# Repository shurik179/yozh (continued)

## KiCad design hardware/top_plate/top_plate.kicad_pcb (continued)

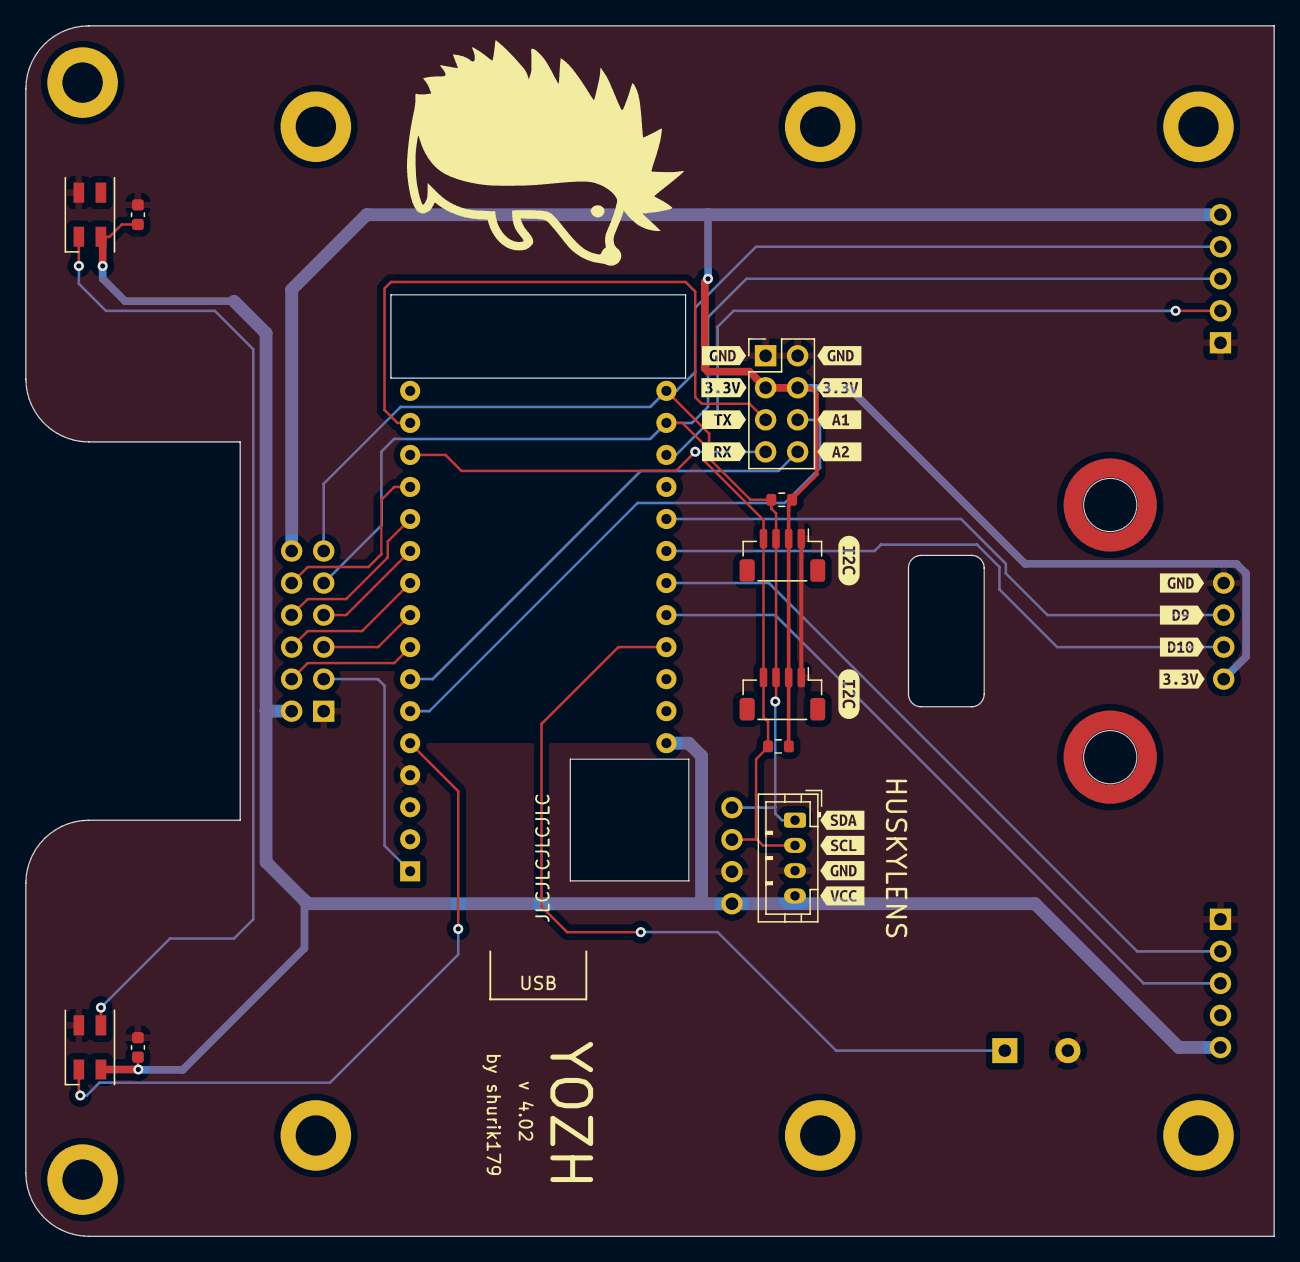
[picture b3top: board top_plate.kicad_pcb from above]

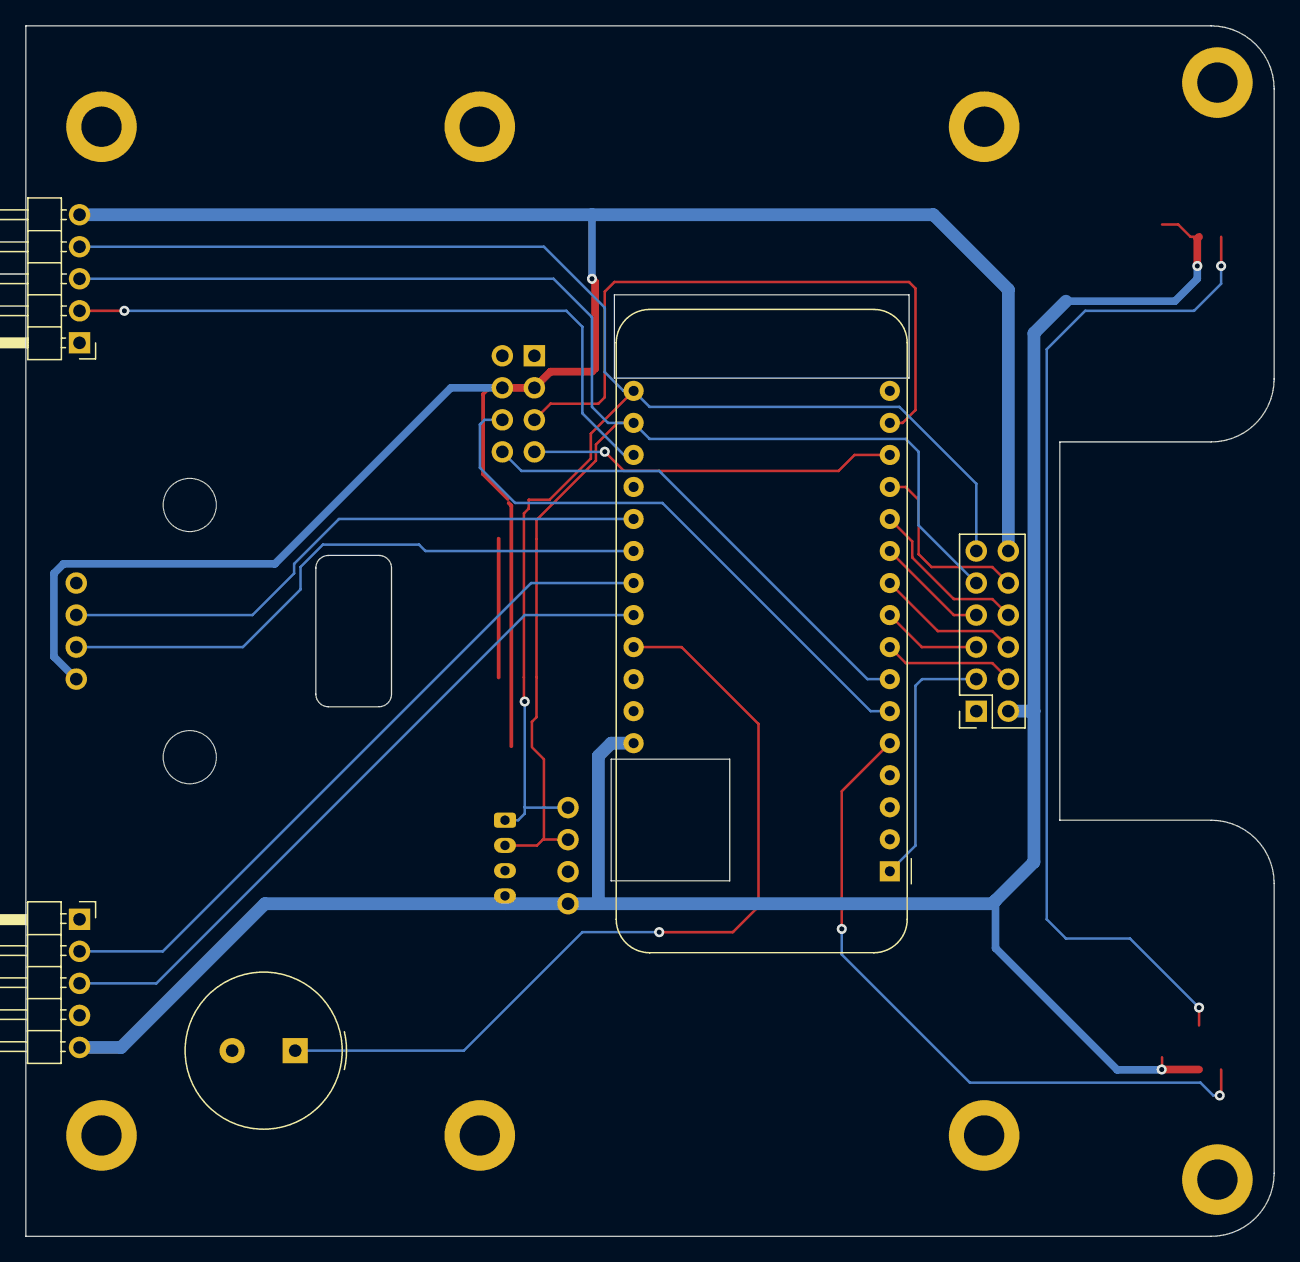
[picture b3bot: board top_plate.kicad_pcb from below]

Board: 2 copper layers, 99.0 x 96.0 mm, 37 parts (5 on the bottom side), 24 nets.

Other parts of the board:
M1, M2: SMTSO3035; mounting_SMD_NUT_M3_H6mm
kibuzzard-653BCB65, kibuzzard-653BCB65#2: G***; kibuzzard-653BCB65
kibuzzard-653BCCF1, kibuzzard-653BCCF1#2: G***; kibuzzard-653BCCF1
kibuzzard-653BCD2B: G***; kibuzzard-653BCD2B
kibuzzard-653BCD4B: G***; kibuzzard-653BCD4B
kibuzzard-653BCD42: G***; kibuzzard-653BCD42
kibuzzard-653BCDC1, kibuzzard-653BCDC1#2: G***; kibuzzard-653BCDC1
kibuzzard-653BCDD4: G***; kibuzzard-653BCDD4
kibuzzard-653BCDDF: G***; kibuzzard-653BCDDF
kibuzzard-653BCDE7: G***; kibuzzard-653BCDE7
kibuzzard-653BCECF: G***; kibuzzard-653BCECF
kibuzzard-653BCED5: G***; kibuzzard-653BCED5
kibuzzard-653BCEE0: G***; kibuzzard-653BCEE0
kibuzzard-653BCF3B: G***; kibuzzard-653BCF3B
kibuzzard-653BCF4B: G***; kibuzzard-653BCF4B
kibuzzard-653BCF42: G***; kibuzzard-653BCF42

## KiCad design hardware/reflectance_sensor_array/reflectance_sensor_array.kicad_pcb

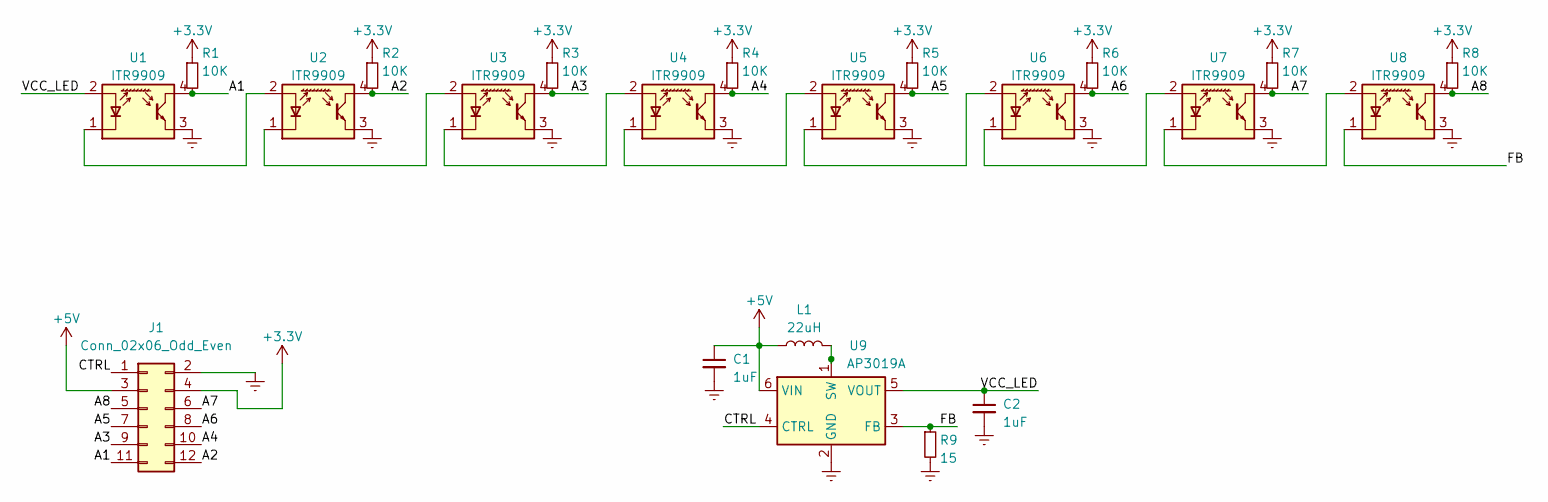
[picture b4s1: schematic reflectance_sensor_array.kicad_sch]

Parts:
C1, C2: 1uF; C_0603_1608Metric
J1: Conn_02x06_Odd_Even; PinHeader_2x06_P2.54mm_Vertical
L1: 22uH; L_Taiyo-Yuden_NR-60xx
R1, R2, R3, R4, R5, R6, R7, R8: 10K; R_0603_1608Metric
R9: 15; R_0603_1608Metric
U1, U2, U3, U4, U5, U6, U7, U8: ITR9909; Everlight_ITR9909
U9: AP3019A; TSOT-23-6

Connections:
+3V3: J1.4, R1.1, R2.1, R3.1, R4.1, R5.1, R6.1, R7.1, R8.1
+5V: C1.1, J1.3, L1.1, U9.6 (VIN)
/A1: J1.11, R1.2, U1.4 (C)
/A2: J1.12, R2.2, U2.4 (C)
/A3: J1.9, R3.2, U3.4 (C)
/A4: J1.10, R4.2, U4.4 (C)
/A5: J1.7, R5.2, U5.4 (C)
/A6: J1.8, R6.2, U6.4 (C)
/A7: J1.6, R7.2, U7.4 (C)
/A8: J1.5, R8.2, U8.4 (C)
/CTRL: J1.1, U9.4 (CTRL)
/FB: R9.1, U8.1 (K), U9.3 (FB)
/VCC_LED: C2.1, U1.2 (A), U9.5 (VOUT)
GNDREF: C1.2, C2.2, J1.2, R9.2, U1.3 (E), U2.3 (E), U3.3 (E), U4.3 (E), U5.3 (E), U6.3 (E), U7.3 (E), U8.3 (E), U9.2 (GND)
unnamed: L1.2, U9.1 (SW)
unnamed: U1.1 (K), U2.2 (A)
unnamed: U2.1 (K), U3.2 (A)
unnamed: U3.1 (K), U4.2 (A)
unnamed: U4.1 (K), U5.2 (A)
unnamed: U5.1 (K), U6.2 (A)
unnamed: U6.1 (K), U7.2 (A)
unnamed: U7.1 (K), U8.2 (A)

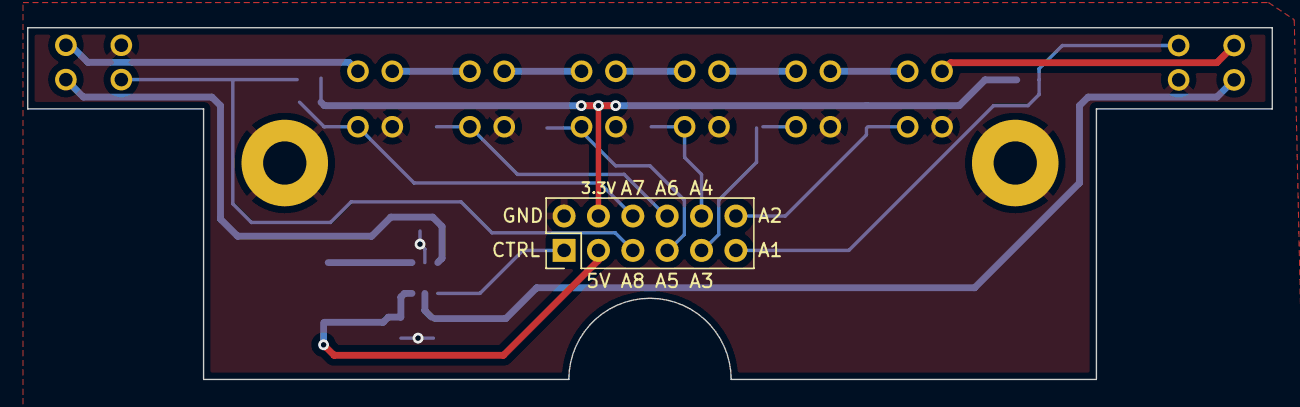
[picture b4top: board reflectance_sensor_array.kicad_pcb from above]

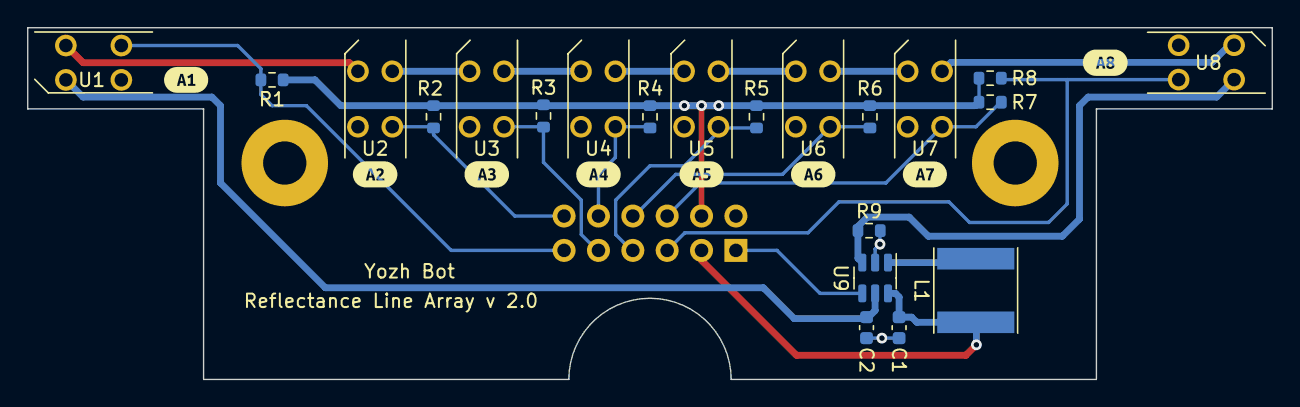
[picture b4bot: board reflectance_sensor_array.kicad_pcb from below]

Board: 2 copper layers, 92.0 x 26.0 mm, 30 parts (29 on the bottom side), 22 nets.

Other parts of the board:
svg2mod, svg2mod#2, svg2mod#3, svg2mod#4, svg2mod#5, svg2mod#6, svg2mod#7, svg2mod#8: G***; svg2mod

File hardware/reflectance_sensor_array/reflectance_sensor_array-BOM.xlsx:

Component | Description | Part Number | References | Value | Footprint | Quantity Per PCB | Side | Datasheet | LCSC | Comment
1 | SMD capacitor, 0603, 1uF |  | C1 C2 | 1uF | C_0603_1608Metric | 2 | Bottom | ~ | C15849 | generic
2 | 2*6 male header, 0.1", 15mm length |  | J1 | Conn_02x06_Odd_Even | PinHeader_2x06_P2.54mm_Vertical | 1 | Top | https://www.aliexpress.com/item/32893947629.html?spm=a2g0s.9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 |  | 2*40 header broken into 2*6 pieces
3 | Inductor, 22uH | NRS6014T220MMGG | L1 | 22uH | L_Taiyo-Yuden_NR-60xx | 1 | Bottom | ~ | C222982
4 | SMD resistor, 0603, 15 Ohm |  | R9 | 15 | R_0603_1608Metric | 1 | Bottom | ~ | C22810 | generic
5 | SMD resistor, 0603, 10K |  | R1 R2 R3 R4 R5 R6 R7 R8 | 10K | R_0603_1608Metric | 8 | Bottom | ~ | C25804 | generic
6 | White LED Step-Up Converter, 1.2Mhz, TSOT23-6 | AP3019AKTR | U9 | AP3019A | TSOT-23-6 | 1 | Bottom | https://www.diodes.com/assets/Datasheets/AP3019A.pdf | C44956
7 | Subminiature Reflective Optical Sensor, DIP-like THT-package | ITR9909 | U1 U2 U3 U4 U5 U6 U7 U8 | ITR9909 | Everlight_ITR9909 | 8 | Bottom | https://everlighteurope.com/index.php?controller=attachment&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 | C53399

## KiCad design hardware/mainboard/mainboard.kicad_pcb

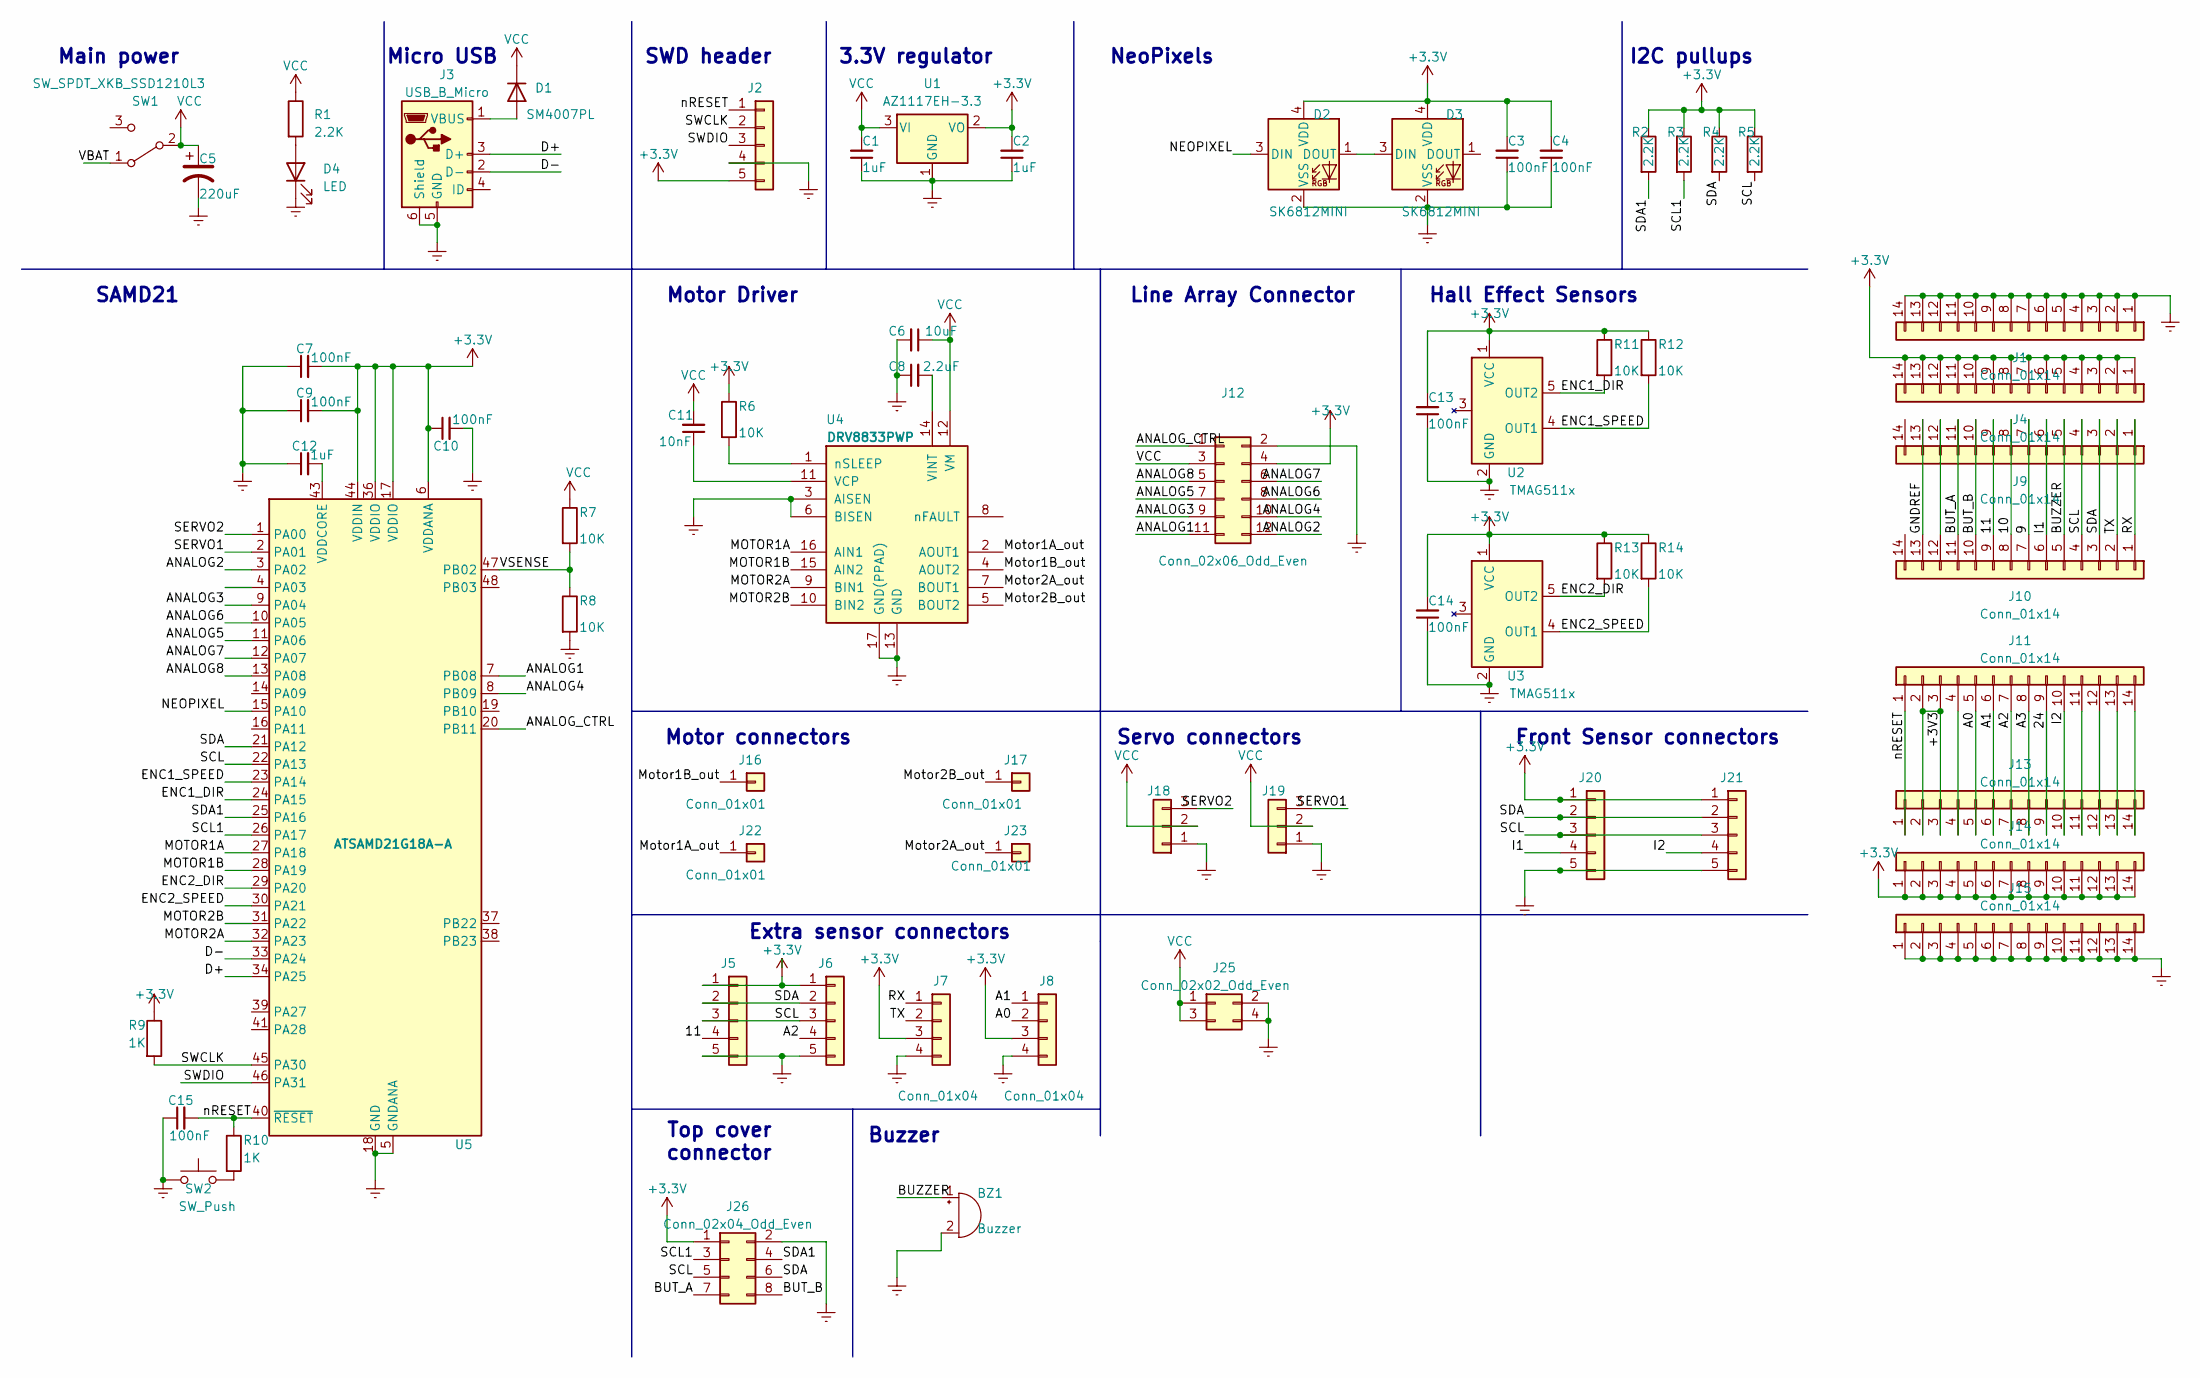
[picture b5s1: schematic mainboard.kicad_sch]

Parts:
BZ1: Buzzer; Buzzer_TDK_PS1240P02BT_D12.2mm_H6.5mm
C1, C2, C12: 1uF; C_0603_1608Metric; LCSC C15849
C3, C4, C7, C9, C10, C13, C14, C15: 100nF; C_0603_1608Metric; LCSC C14663
C5: 220uF; C_Radial_D8.0mm_H7.0mm_P3.50mm
C6: 10uF; C_0805_2012Metric; LCSC C15850
C8: 2.2uF; C_0603_1608Metric; LCSC C23630
C11: 10nF; C_0603_1608Metric; LCSC C57112
D1: SM4007PL; D_SOD-123F; LCSC C64898
D2, D3: SK6812MINI; LED_SK6812MINI_PLCC4_3.5x3.5mm_P1.75mm
D4: LED; LED_0603_1608Metric
J1, J4, J9, J13, J14, J15: Conn_01x14; PinHeader_1x14_P2.54mm_Vertical
J2: Conn_01x05; PinSocket_1x05_P2.54mm_Lock
J3: USB_B_Micro; USB_Micro-B_Amphenol_10118194_Horizontal; LCSC C145779
J5, J6, J20, J21: Conn_01x05; PinHeader_1x05_P2.54mm_Vertical
J7, J8: Conn_01x04; JST_PH_B4B-PH-K_1x04_P2.00mm_Vertical
J10, J11: Conn_01x14; PinSocket_1x14_P2.54mm_Vertical
J12: Conn_02x06_Odd_Even; PinSocket_2x06_P2.54mm_Vertical
J16, J17, J22, J23: Conn_01x01; connector-1p-generic-nosilk
J18, J19: Conn_01x03; PinHeader_1x03_P2.54mm_Vertical
J25: Conn_02x02_Odd_Even; PinHeader_2x02_P2.54mm_Vertical
J26: Conn_02x04_Odd_Even; PinSocket_2x04_P2.54mm_Vertical
R1: 2.2K; R_0603_1608Metric; LCSC C21190
R2, R3, R4, R5: 2.2K; R_0603_1608Metric; LCSC C4190
R6, R7, R8, R11, R12, R13, R14: 10K; R_0603_1608Metric; LCSC C25804
R9, R10: 1K; R_0603_1608Metric; LCSC C21190
SW1: SW_SPDT_XKB_SSD1210L3; SW_XKB_SS12D10L3
SW2: SW_Push; SW_SPST_HRO-K2-1808SN
U1: AZ1117EH-3.3; SOT-223; LCSC C108494
U2, U3: TMAG511x; SOT-23-5
U4: DRV8833PWP; HTSSOP-16-1EP_4.4x5mm_P0.65mm_EP3.4x5mm_Mask2.46x2.31mm_The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; LCSC C50506
U5: ATSAMD21G18A-A; QFP-48_7x7_Pitch0.5mm_reduced

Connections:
/9: J9.7, J10.7
/10: J9.8, J10.8
/11: J5.4, J9.9, J10.9
/24: J11.9, J13.9
/A0: J8.2, J11.5, J13.5
/A1: J8.1, J11.6, J13.6
/A2: J6.4, J11.7, J13.7
/A3: J11.8, J13.8
/ANALOG1: J12.11, U5.7 (PB08)
/ANALOG2: J12.12, U5.3 (PA02)
/ANALOG3: J12.9, U5.9 (PA04)
/ANALOG4: J12.10, U5.8 (PB09)
/ANALOG5: J12.7, U5.11 (PA06)
/ANALOG6: J12.8, U5.10 (PA05)
/ANALOG7: J12.6, U5.12 (PA07)
/ANALOG8: J12.5, U5.13 (PA08)
/ANALOG_CTRL: J12.1, U5.20 (PB11)
/BUT_A: J9.11, J10.11, J26.7
/BUT_B: J9.10, J10.10, J26.8
/BUZZER: BZ1.1 (-), J9.5, J10.5
/D+: J3.3 (D+), U5.34 (PA25)
/D-: J3.2 (D-), U5.33 (PA24)
/ENC1_DIR: R11.2, U2.5 (OUT2), U5.24 (PA15)
/ENC1_SPEED: R12.2, U2.4 (OUT1), U5.23 (PA14)
/ENC2_DIR: R13.2, U3.5 (OUT2), U5.29 (PA20)
/ENC2_SPEED: R14.2, U3.4 (OUT1), U5.30 (PA21)
/I1: J9.6, J10.6, J20.4
/I2: J11.10, J13.10, J21.4
/MOTOR1A: U4.16 (AIN1), U5.27 (PA18)
/MOTOR1B: U4.15 (AIN2), U5.28 (PA19)
/MOTOR2A: U4.9 (BIN1), U5.32 (PA23)
/MOTOR2B: U4.10 (BIN2), U5.31 (PA22)
/Motor1A_out: J22.1, U4.2 (AOUT1)
/Motor1B_out: J16.1, U4.4 (AOUT2)
/Motor2A_out: J23.1, U4.7 (BOUT1)
/Motor2B_out: J17.1, U4.5 (BOUT2)
/NEOPIXEL: D2.3 (DIN), U5.15 (PA10)
/RX: J7.1, J9.1, J10.1
/SCL: J5.3, J6.3, J9.4, J10.4, J20.3, J21.3, J26.5, R5.2, U5.22 (PA13)
/SCL1: J26.3, R3.2, U5.26 (PA17)
/SDA: J5.2, J6.2, J9.3, J10.3, J20.2, J21.2, J26.6, R4.2, U5.21 (PA12)
/SDA1: J26.4, R2.2, U5.25 (PA16)
/SERVO1: J19.3, U5.2 (PA01)
/SERVO2: J18.3, U5.1 (PA00)
/SWCLK: J2.2, R9.2, U5.45 (PA30)
/SWDIO: J2.3, U5.46 (PA31)
/TX: J7.2, J9.2, J10.2
/VBAT: SW1.1 (A)
/VSENSE: R7.2, R8.1, U5.47 (PB02)
/nRESET: C15.2, J2.1, J11.1, J13.1, R10.1, U5.40 (~RESET)
GNDREF: BZ1.2 (+), C1.1, C2.1, C3.1, C4.1, C5.2, C6.2, C7.1, C8.1, C9.1, C10.2, C12.1, C13.1, C14.1, C15.1, D2.2 (VSS), D3.2 (VSS), D4.1 (K), J1.1, J1.2, J1.3, J1.4, J1.5, J1.6, J1.7, J1.8, J1.9, J1.10, J1.11, J1.12, J1.13, J1.14, J2.4, J3.5 (GND), J3.6 (Shield), J5.5, J6.5, J7.4, J8.4, J9.13, J10.13, J12.2, J15.1, J15.2, J15.3, J15.4, J15.5, J15.6, J15.7, J15.8, J15.9, J15.10, J15.11, J15.12, J15.13, J15.14, J18.1, J19.1, J20.5, J21.5, J25.2, J25.4, J26.2, R8.2, SW2.1, U1.1 (GND), U2.2 (GND), U3.2 (GND), U4.3 (AISEN), U4.6 (BISEN), U4.13 (GND), U4.17 (GND(PPAD)), U5.5 (GNDANA), U5.18 (GND), U5.35 (GND), U5.42 (GND)
unnamed: C8.2, U4.14 (VINT)
unnamed: C11.1, U4.11 (VCP)
unnamed: C12.2, U5.43 (VDDCORE)
unnamed: D1.2 (A), J3.1 (VBUS)
unnamed: D2.1 (DOUT), D3.3 (DIN)
unnamed: D4.2 (A), R1.2
unnamed: J9.12, J10.12
unnamed: J11.4, J13.4
unnamed: J11.11, J13.11
unnamed: J11.12, J13.12
unnamed: J11.13, J13.13
unnamed: J11.14, J13.14
unnamed: R6.2, U4.1 (nSLEEP)
unnamed: R10.2, SW2.2
VCC: C1.2, C5.1, C6.1, C11.2, D1.1 (K), J12.3, J18.2, J19.2, J25.1, J25.3, R1.1, R7.1, SW1.2 (B), U1.3 (VI), U4.12 (VM)

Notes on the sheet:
Hall Effect Sensors
Extra sensor connectors
Line Array Connector
SWD header
3.3V regulator
Top cover connector
Servo connectors
Front Sensor connectors
NeoPixels
Motor Driver
SAMD21
Main power
Motor connectors
I2C pullups
Buzzer
Micro USB

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
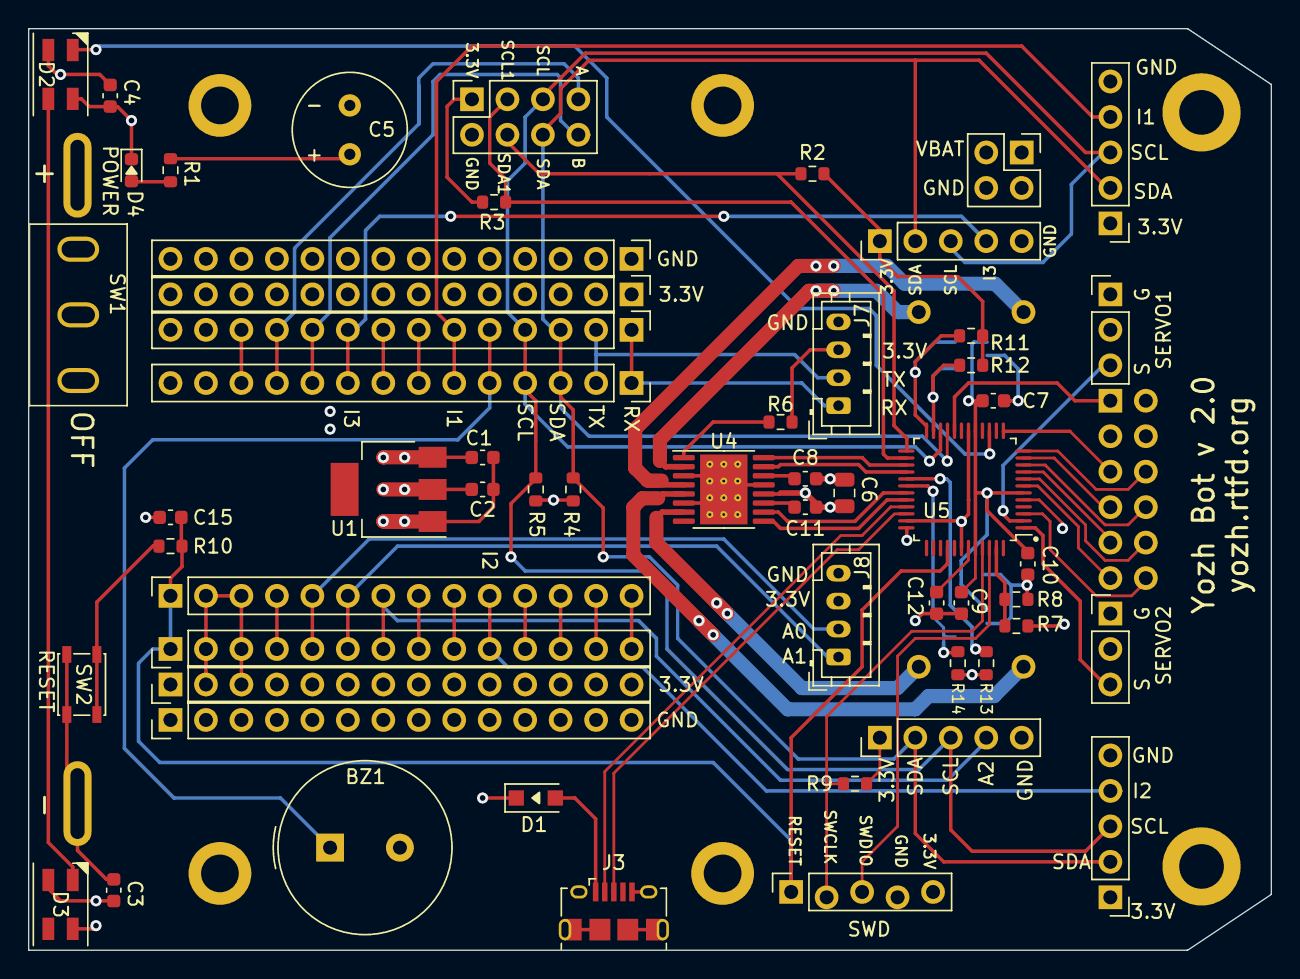
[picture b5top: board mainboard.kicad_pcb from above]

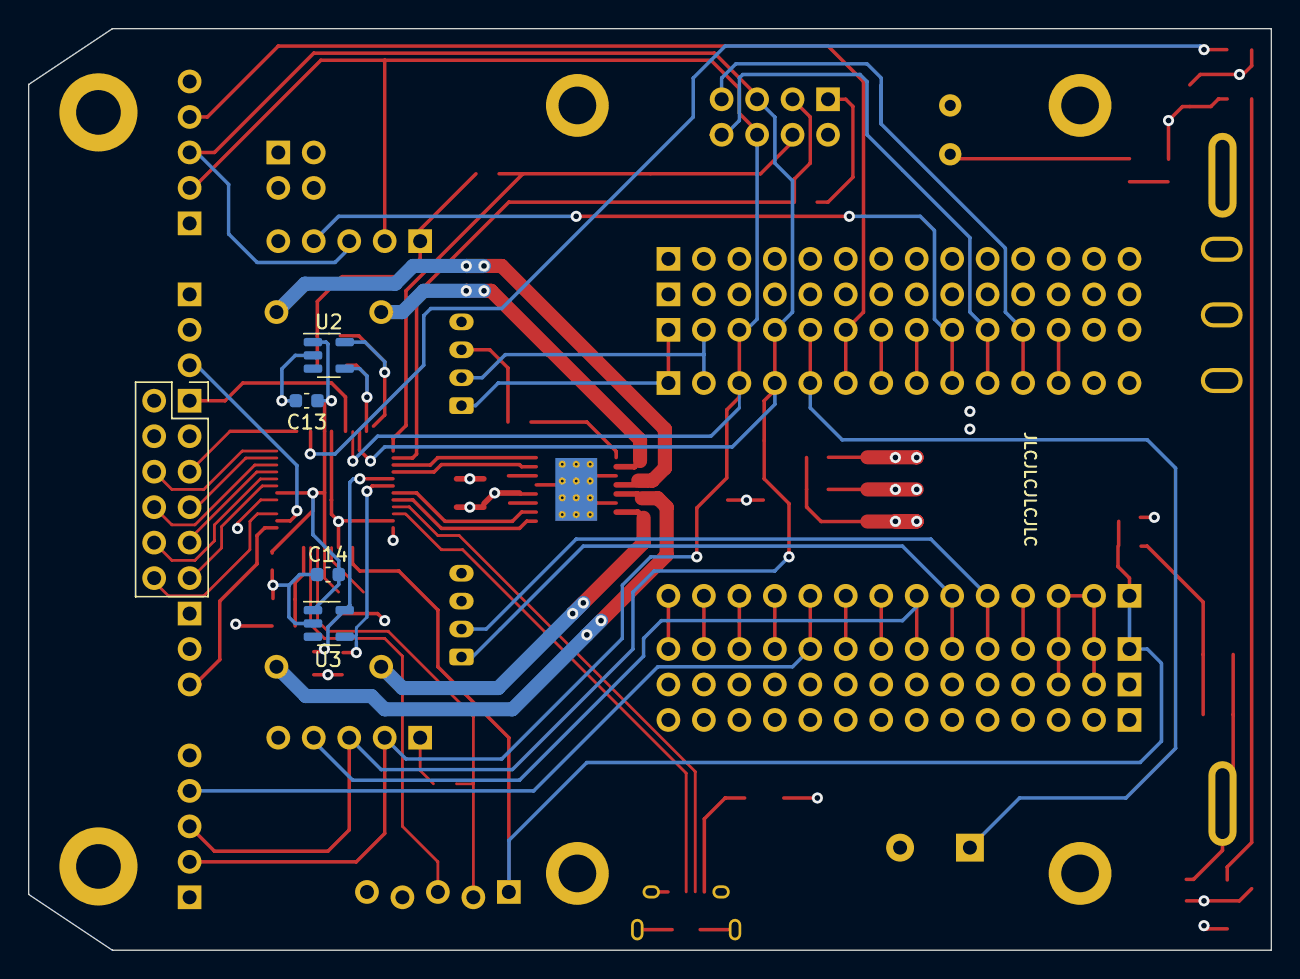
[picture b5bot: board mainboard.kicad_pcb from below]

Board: 4 copper layers, 89.0 x 66.0 mm, 66 parts (5 on the bottom side), 66 nets.

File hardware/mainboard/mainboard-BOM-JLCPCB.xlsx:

Comment | Designator | Footprint | LCSC
10nF | C11 | 0603 | C57112
100nF | C3 C4 C7 C9 C10 C15 | 0603 | C14663
1uF | C1 C2 C12 | 0603 | C15849
2.2uF | C8 | 0603 | C23630
10uF | C6 | 0805 | C15850
220uF | C5 | C_Radial_D8.0mm_H7.0mm_P3.50mm | C45072
LED, Green | D4 | LED_0603_1608Metric | C72043
SM4007PL | D1 | D_SOD-123F | C64898
 | J3 | USB_Micro-B_Amphenol_10118194_Horizontal | C132563
1K | R9 R10 | 0603 | C21190
2.2K | R1 R2 R3 R4 R5 | 0603 | C4190
10K | R6 R7 R8 R11 R12 R13 R14 | 0603 | C25804
 | SW2 | SW_SPST_HRO-K2-1808SN | C92589
 | SW1 | SW_XKB_SS12D10L3 | C319013
ATSAMD21G18A-AU | U5 | QFP-48_7x7_Pitch0.5mm_reduced | C78624
AZ1117EH-3.3TRG1 | U1 | SOT-223 | C108494
DRV8833PWP | U4 | HTSSOP-16-1EP_4.4x5mm_P0.65mm_EP3.4x5mm_Mask2.46x2.31mm_ThermalVias_reduced | C50506
 | BZ1 | Buzzer_TDK_PS1240P02BT_D12.2mm_H6.5mm | C76871

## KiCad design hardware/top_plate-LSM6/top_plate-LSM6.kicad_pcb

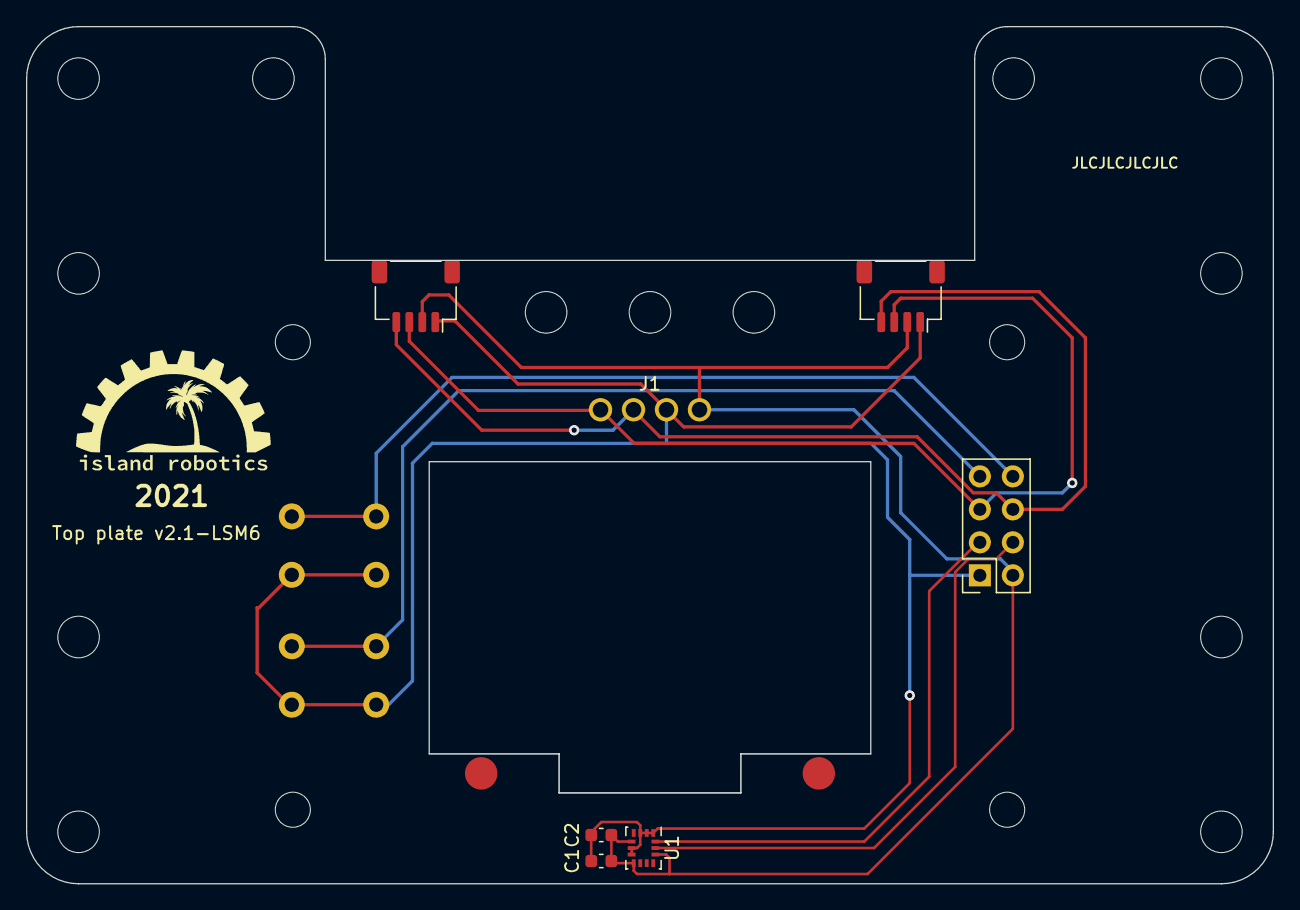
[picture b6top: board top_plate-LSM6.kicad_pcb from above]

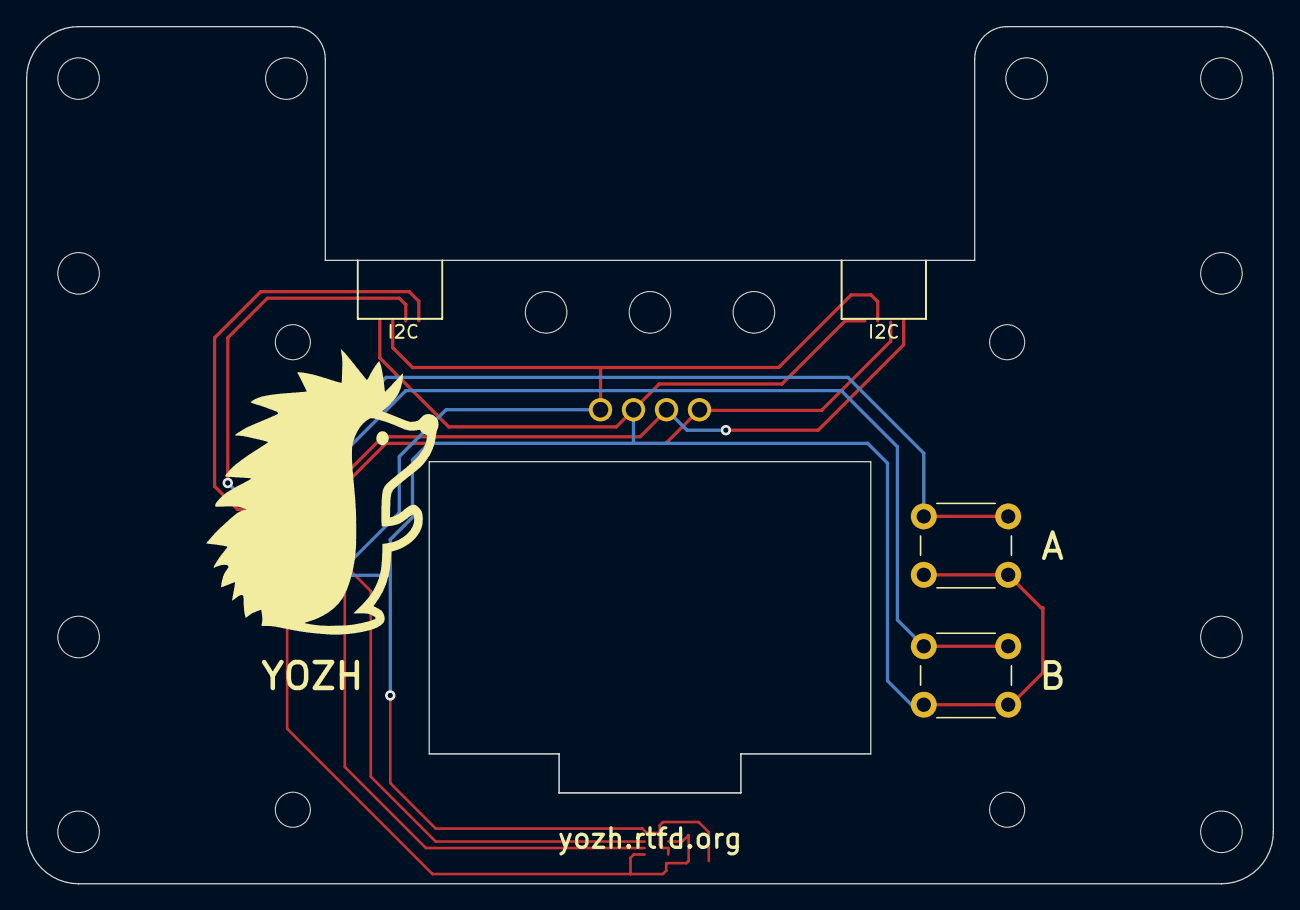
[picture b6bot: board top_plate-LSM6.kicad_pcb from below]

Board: 2 copper layers, 96.0 x 66.0 mm, 9 parts (2 on the bottom side), 8 nets.

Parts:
C1, C2: 100nF; C_0603_1608Metric
J1: Conn_01x04_Male; OLED_128x64_1_3in
J2, J3: Conn_01x04; JST_SH_SM04B-SRSS-TB_1x04-1MP_P1.00mm_Horizontal
J4: Conn_02x04_Odd_Even; PinSocket_2x04_P2.54mm_Vertical
SW1, SW2: SW_Push; SW_PUSH_6mm_H4.3mm
U1: LSM6DSL; LGA-14_3x2.5mm_P0.5mm_LayoutBorder3x4y

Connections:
+3V3: C1.1, C2.1, J1.1, J2.2, J3.2, J4.2, U1.5 (VDDIO), U1.8 (VDD), U1.12 (CS)
/A: J4.8, SW1.1
/B: J4.7, SW2.1
/SCL: J1.3, J2.4, J3.4, J4.6
/SCL1: J4.4, U1.13 (SCL)
/SDA: J1.4, J2.3, J3.3, J4.5
/SDA1: J4.3, U1.14 (SDA)
GNDREF: C1.2, C2.2, J1.2, J2.1, J3.1, J4.1, SW1.2, SW2.2, U1.1 (SDO/SA0), U1.2 (SDX), U1.3 (SCX), U1.6 (GND), U1.7 (GND)

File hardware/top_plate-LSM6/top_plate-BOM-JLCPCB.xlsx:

Comment | Designator | Footprint | LCSC
100nF | C1 C2 | 0603 | C14663
LSM6DSL | U1 | LGA14 | C126672
SM04B-SRSS-TB | J2 J3 |  | C145956
2*4 female header, 0.1" | J4 |  | C92271

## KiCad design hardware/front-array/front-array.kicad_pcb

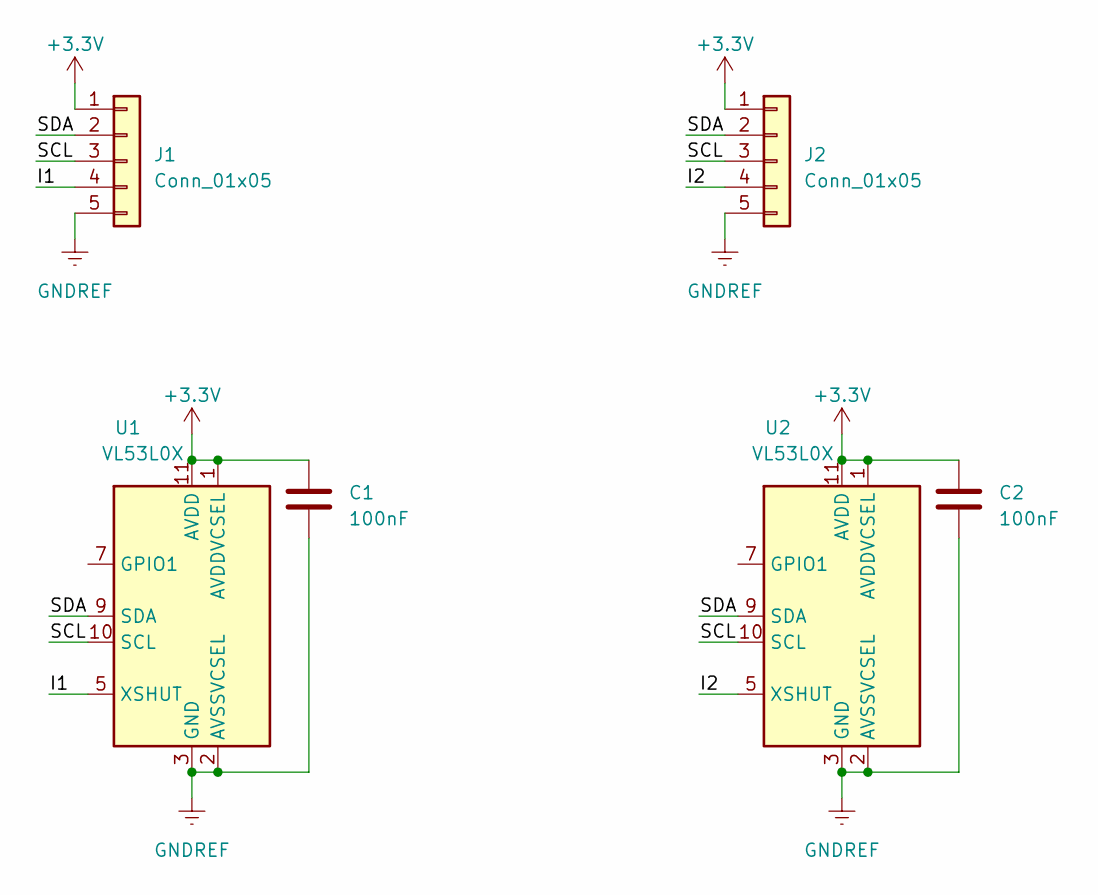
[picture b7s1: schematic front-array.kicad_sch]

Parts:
C1, C2: 100nF; C_0603_1608Metric
J1, J2: Conn_01x05; PinSocket_1x05_P2.54mm_Horizontal
U1, U2: VL53L0X; ST_VL53L1x

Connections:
+3V3: C1.1, C2.1, J1.1, J2.1, U1.1 (AVDDVCSEL), U1.11 (AVDD), U2.1 (AVDDVCSEL), U2.11 (AVDD)
/I1: J1.4, U1.5 (XSHUT)
/I2: J2.4, U2.5 (XSHUT)
/SCL: J1.3, J2.3, U1.10 (SCL), U2.10 (SCL)
/SDA: J1.2, J2.2, U1.9 (SDA), U2.9 (SDA)
GNDREF: C1.2, C2.2, J1.5, J2.5, U1.2 (AVSSVCSEL), U1.3 (GND), U1.4 (GND), U1.6 (GND), U1.12 (GND), U2.2 (AVSSVCSEL), U2.3 (GND), U2.4 (GND), U2.6 (GND), U2.12 (GND)

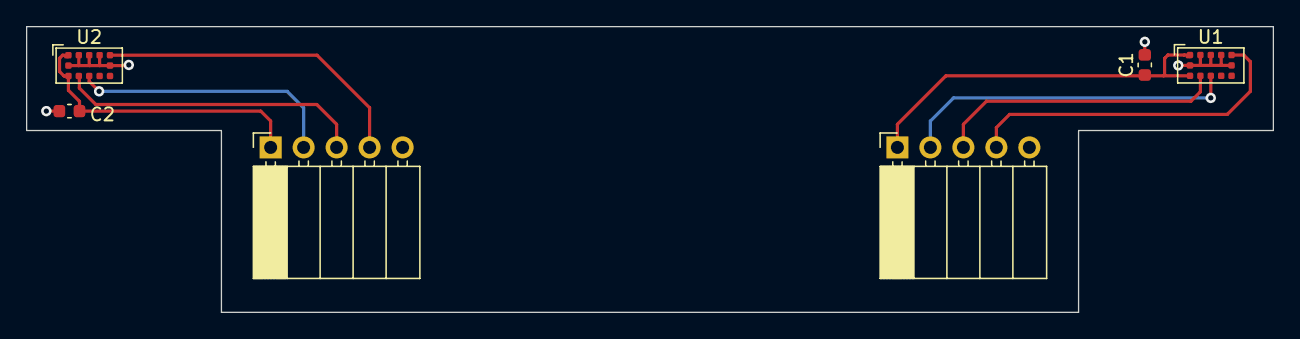
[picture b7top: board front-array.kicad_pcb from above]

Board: 2 copper layers, 96.0 x 22.0 mm, 6 parts (0 on the bottom side), 6 nets.

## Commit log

2021-09-27 Initial directory structure created
2021-10-30 docs update
2021-10-30 fix filename
2021-10-30 adding hardware files
    Design files for reflectance sensor array
2021-10-30 Updated the assembly guide
2021-10-31 docs
2021-11-01 quickstart started
2021-11-01 hardware files for top plate
2021-11-02 quickstart updated
2021-11-02 quickstart update
2021-11-02 started library reference
2021-11-02 library reference updated
2021-11-03 added KiCad files for front array
2021-11-04 copied mainboard KiCad files
2021-11-05 3d modeling update
2021-11-06 Mainboard: update BOM, fabrication print
2021-11-24 Major update; version 2.0 almost complete
2021-11-26 updating docs
2021-11-27 docs update - adding photos
2021-11-27 docs updated
2021-11-27 images update
2021-11-27 dos update
2021-11-27 docs updtae
2021-11-27 docs cors-references
2022-01-10 Adding IMU code
2022-01-10 update docs
2022-01-11 cleanup for release 2.0
2022-01-11 more docs cleanup
2022-01-11 added link to 3d model
2022-01-11 adding link to photos
2022-01-12 updating examples
2022-01-18 firmware update
2022-07-11 June2022 update
2022-07-11 binaries update
2022-07-14 build downloadable docs
2023-10-16 updated python library and docs
2023-10-28 final v3 release
2023-10-28 updating docs for new build system
2023-10-28 Creating v4 branch
2023-10-28 Updating license information
2023-10-29 updating license info on software
2023-10-29 more license updates
2023-10-29 adding SPDX license info
2023-10-30 fixing drive and turn issues
2023-10-30 updatign docs
2023-10-30 minor doc fixes
2023-10-30 more docs work
2023-10-30 fix start_forward function
2023-11-01 added board package files
2023-11-06 added board support package
2023-11-06 board support update
2023-11-12 board support package
2023-11-13 new build of support package
2023-11-15 update arduino support package
2023-11-15 updating for v 4.02
2023-11-16 examples and docs updates
2023-11-17 docs update - new images.
2023-11-17 more doc images
2023-11-17 thonny screenshot for docs
2023-11-17 image update
2023-11-18 docs update- added quickstart functions reference
2023-11-18 adding projects
2023-11-18 docs fix
2023-11-18 updating images
2023-11-19 fixing images in docs
2023-11-19 docs fixes
2023-11-20 working on better turns
2023-11-23 fixing typos
2023-11-24 huskylens updates
